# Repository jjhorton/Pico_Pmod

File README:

# Hardware
The aim of this repo is to have a PCB on which I was able to mount a standard
[Raspberry Pi Pico](https://www.raspberrypi.org/products/raspberry-pi-pico/)
and have an extended duel PMod Connector. This would allow me to connect up
the Raspberry Pi Pico upto a range of PMod Boards that I already own, as well
as to connect it upto some of the FPGA boards that I already own though there
PMod connector.

For working with the pre existing PMod Boards I've made a PMod Host board,
this hosts the accessories such as an [Seven Segment display]() or
[PMOD buttons]() 

# Software

## Host Example Software

## Client Example Software

# Licensing

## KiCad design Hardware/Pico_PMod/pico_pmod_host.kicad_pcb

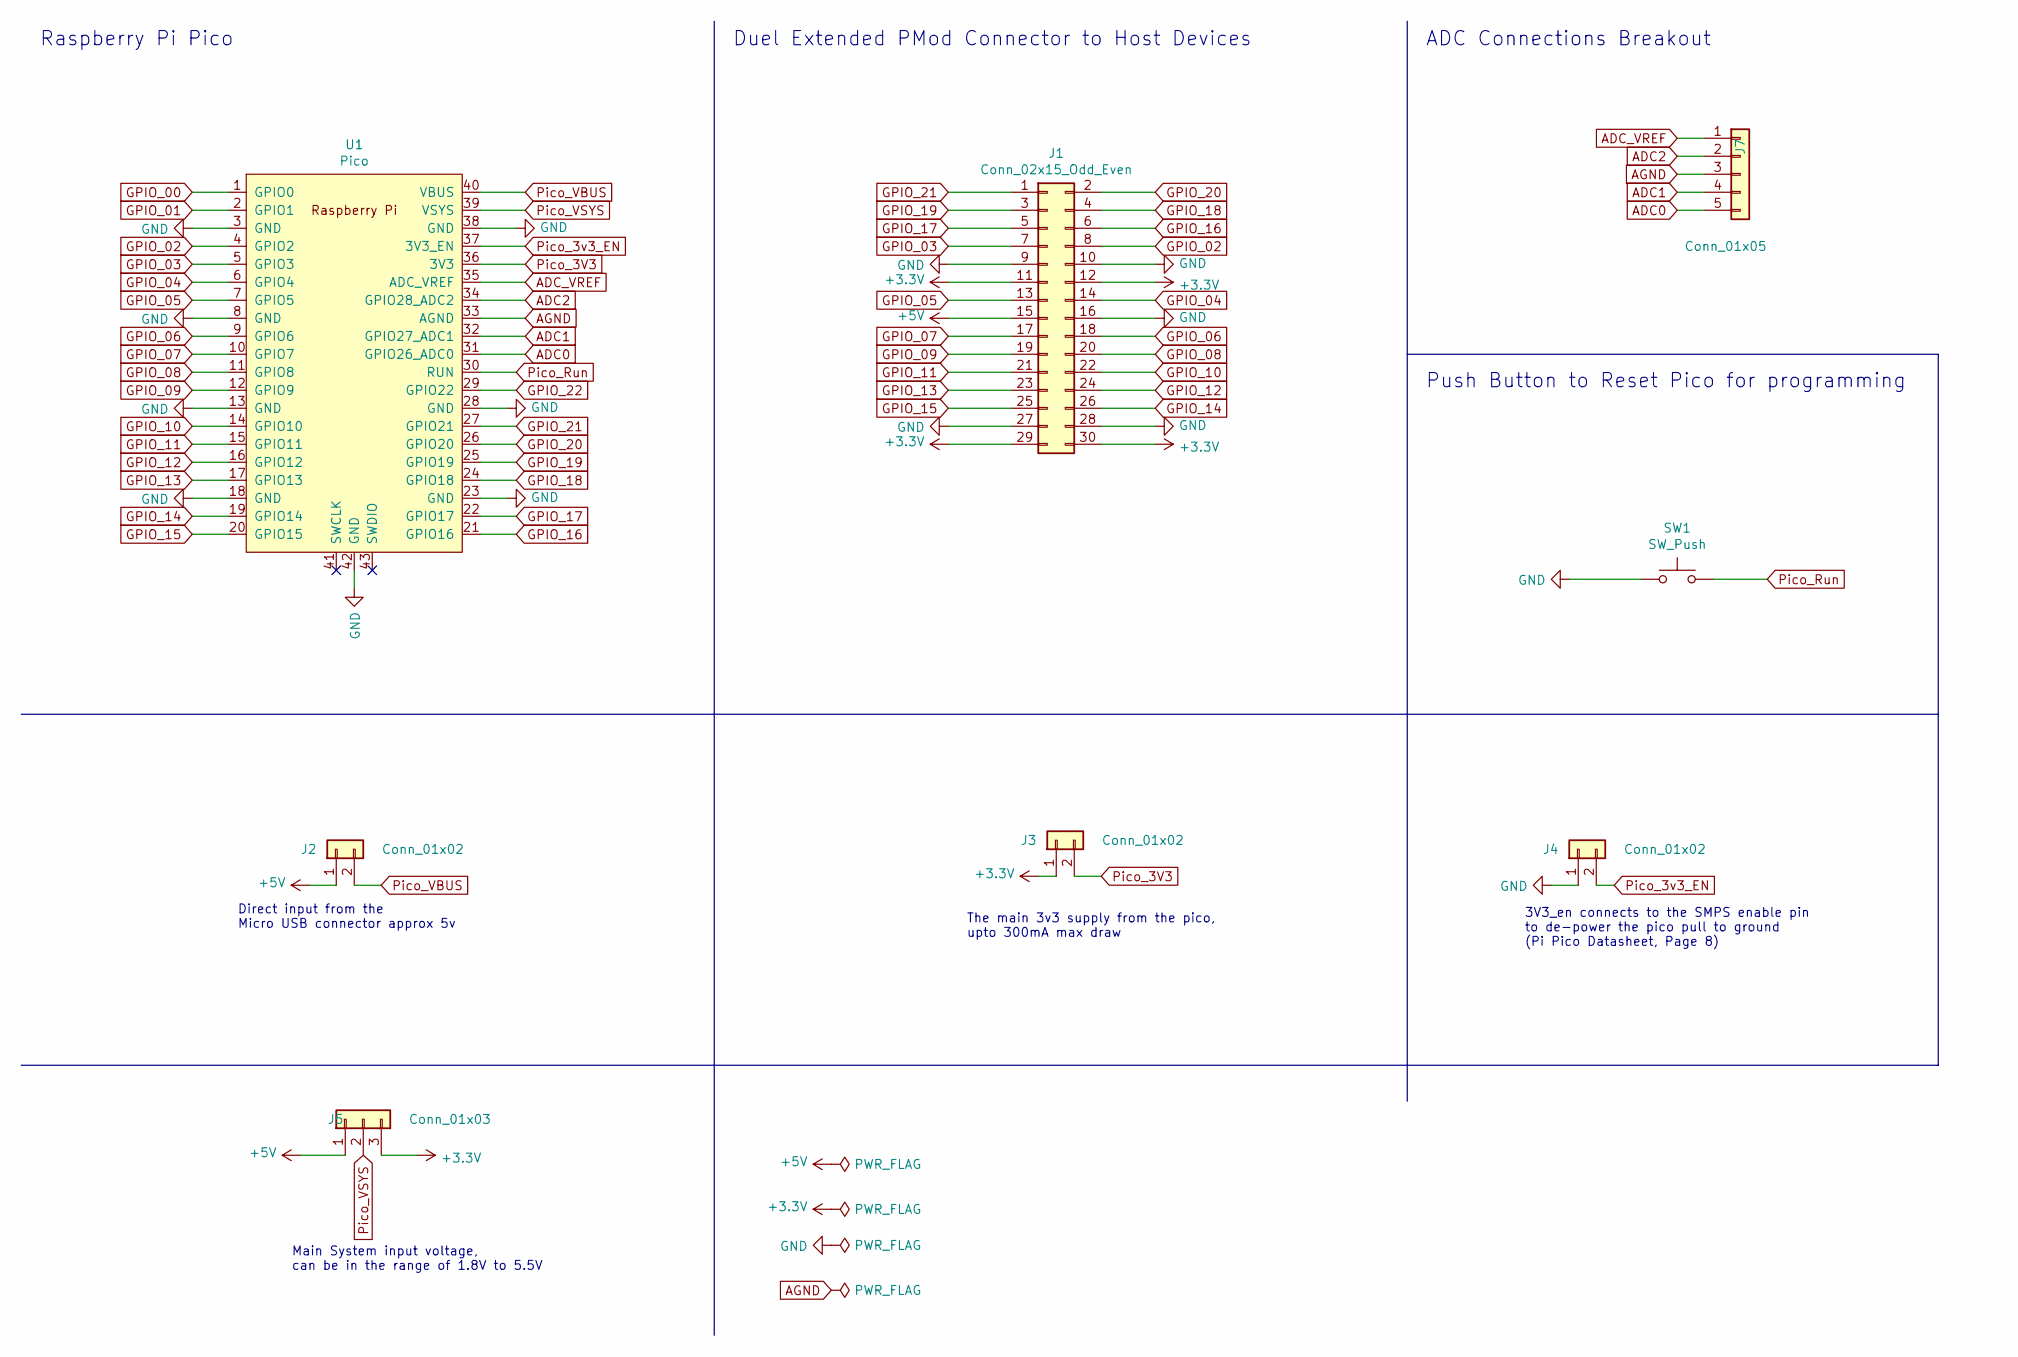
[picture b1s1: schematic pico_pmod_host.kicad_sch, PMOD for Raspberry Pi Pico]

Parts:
J1: Conn_02x15_Odd_Even; PinHeader_2x15_P2.54mm_Vertical
J2, J3, J4: Conn_01x02; PinHeader_1x02_P2.54mm_Vertical
J5: Conn_01x03; PinHeader_1x03_P2.54mm_Vertical
J7: Conn_01x05; PinHeader_1x05_P2.54mm_Vertical
SW1: SW_Push; SW_PUSH_6mm_H4.3mm
U1: Pico; RPi_Pico_SMD_TH

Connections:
+3V3: J1.11, J1.12, J1.29, J1.30, J3.1, J5.3
+5V: J1.15, J2.1, J5.1
ADC0: J7.5, U1.31 (GPIO26_ADC0)
ADC1: J7.4, U1.32 (GPIO27_ADC1)
ADC2: J7.2, U1.34 (GPIO28_ADC2)
ADC_VREF: J7.1, U1.35 (ADC_VREF)
AGND: J7.3, U1.33 (AGND)
GND: J1.9, J1.10, J1.16, J1.27, J1.28, J4.1, SW1.1, U1.3 (GND), U1.8 (GND), U1.13 (GND), U1.18 (GND), U1.23 (GND), U1.28 (GND), U1.38 (GND), U1.42 (GND)
GPIO_00: U1.1 (GPIO0)
GPIO_01: U1.2 (GPIO1)
GPIO_02: J1.8, U1.4 (GPIO2)
GPIO_03: J1.7, U1.5 (GPIO3)
GPIO_04: J1.14, U1.6 (GPIO4)
GPIO_05: J1.13, U1.7 (GPIO5)
GPIO_06: J1.18, U1.9 (GPIO6)
GPIO_07: J1.17, U1.10 (GPIO7)
GPIO_08: J1.20, U1.11 (GPIO8)
GPIO_09: J1.19, U1.12 (GPIO9)
GPIO_10: J1.22, U1.14 (GPIO10)
GPIO_11: J1.21, U1.15 (GPIO11)
GPIO_12: J1.24, U1.16 (GPIO12)
GPIO_13: J1.23, U1.17 (GPIO13)
GPIO_14: J1.26, U1.19 (GPIO14)
GPIO_15: J1.25, U1.20 (GPIO15)
GPIO_16: J1.6, U1.21 (GPIO16)
GPIO_17: J1.5, U1.22 (GPIO17)
GPIO_18: J1.4, U1.24 (GPIO18)
GPIO_19: J1.3, U1.25 (GPIO19)
GPIO_20: J1.2, U1.26 (GPIO20)
GPIO_21: J1.1, U1.27 (GPIO21)
GPIO_22: U1.29 (GPIO22)
Pico_3V3: J3.2, U1.36 (3V3)
Pico_3v3_EN: J4.2, U1.37 (3V3_EN)
Pico_Run: SW1.2, U1.30 (RUN)
Pico_VBUS: J2.2, U1.40 (VBUS)
Pico_VSYS: J5.2, U1.39 (VSYS)

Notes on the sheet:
Duel Extended PMod Connector to Host Devices
Main System input voltage, can be in the range of 1.8V to 5.5V
3V3_en connects to the SMPS enable pin to de-power the pico pull to ground (Pi Pico Datasheet, Page 8)
The main 3v3 supply from the pico, upto 300mA max draw
Push Button to Reset Pico for programming
ADC Connections Breakout
Direct input from the Micro USB connector approx 5v
Raspberry Pi Pico

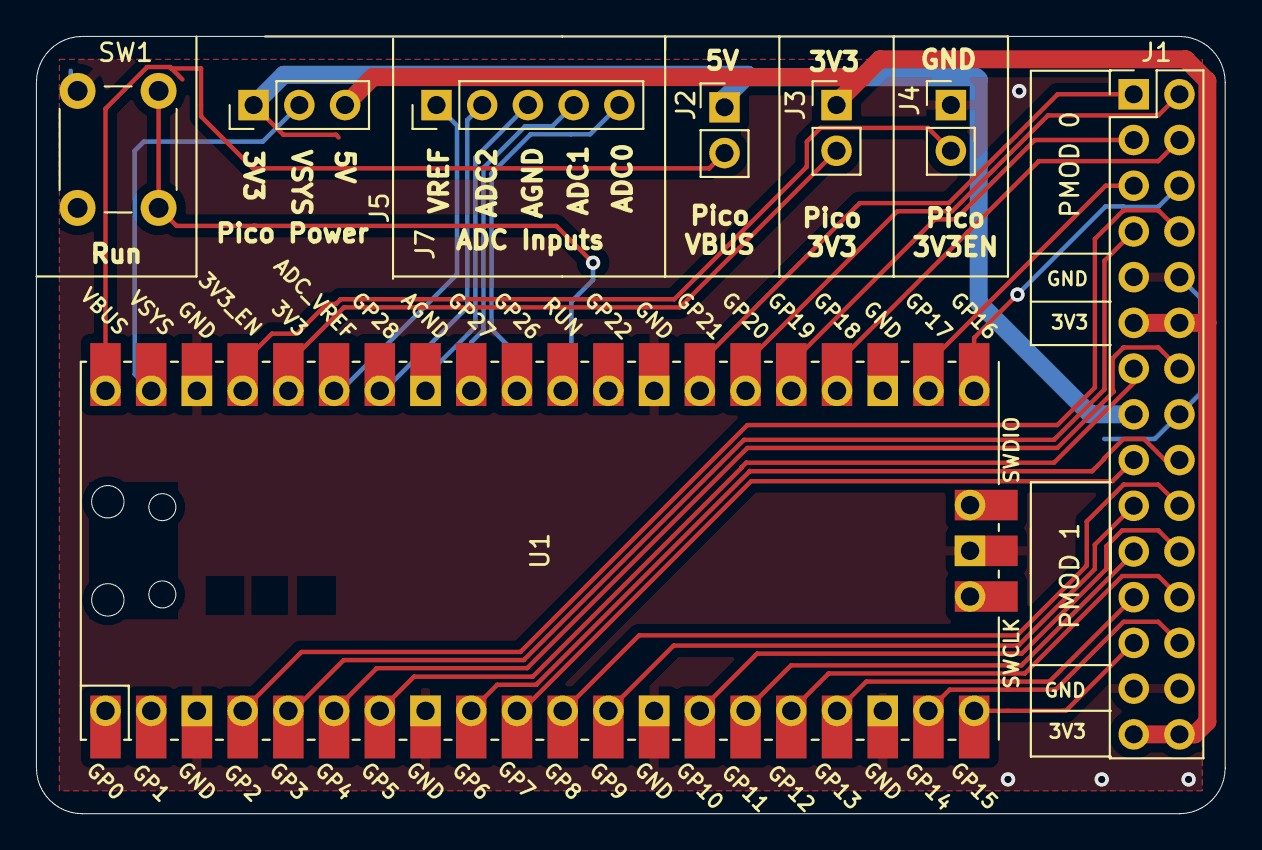
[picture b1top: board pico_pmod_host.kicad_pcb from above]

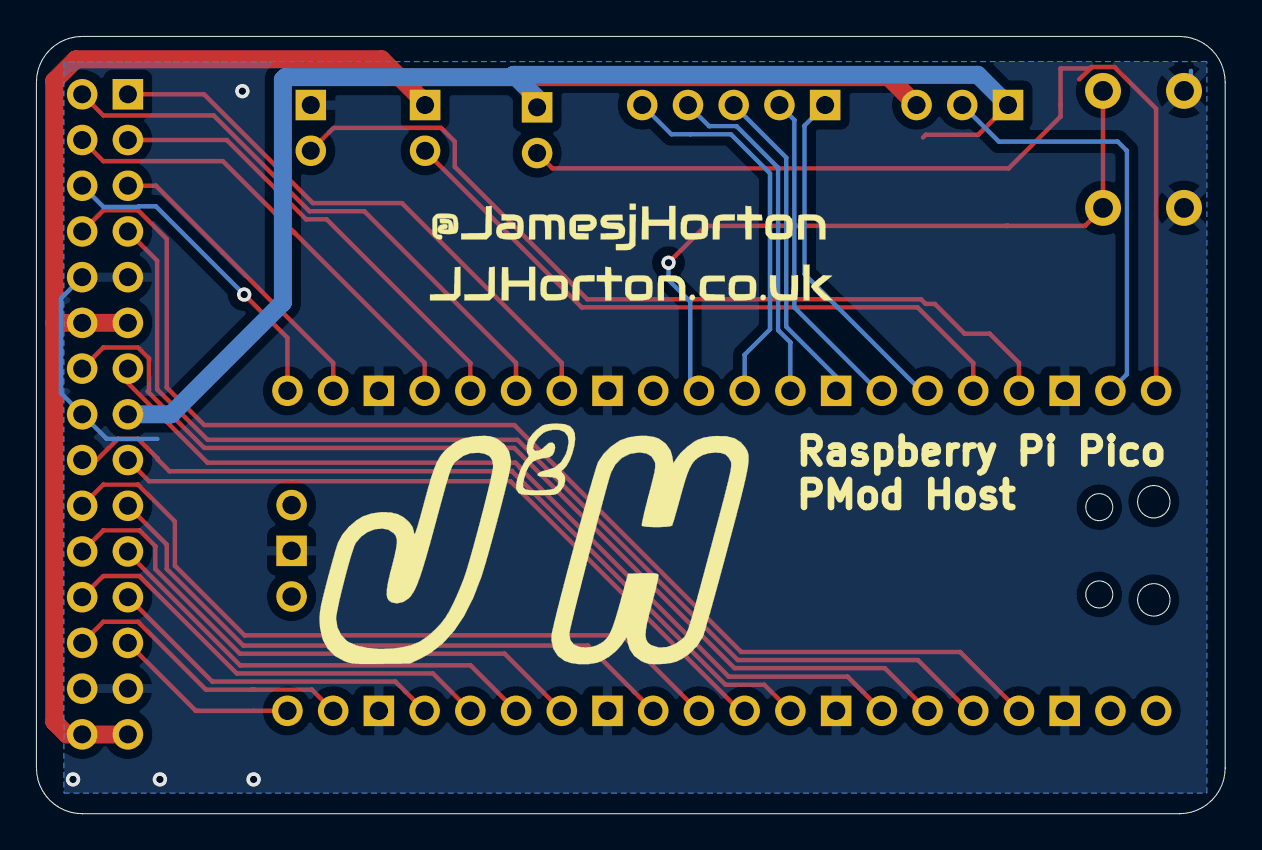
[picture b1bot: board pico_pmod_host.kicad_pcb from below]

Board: 2 copper layers, 66.0 x 43.2 mm, 10 parts (2 on the bottom side), 33 nets.

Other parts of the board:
Logo1: LOGO; Untitled
Logo2: LOGO; ContactDetails_small

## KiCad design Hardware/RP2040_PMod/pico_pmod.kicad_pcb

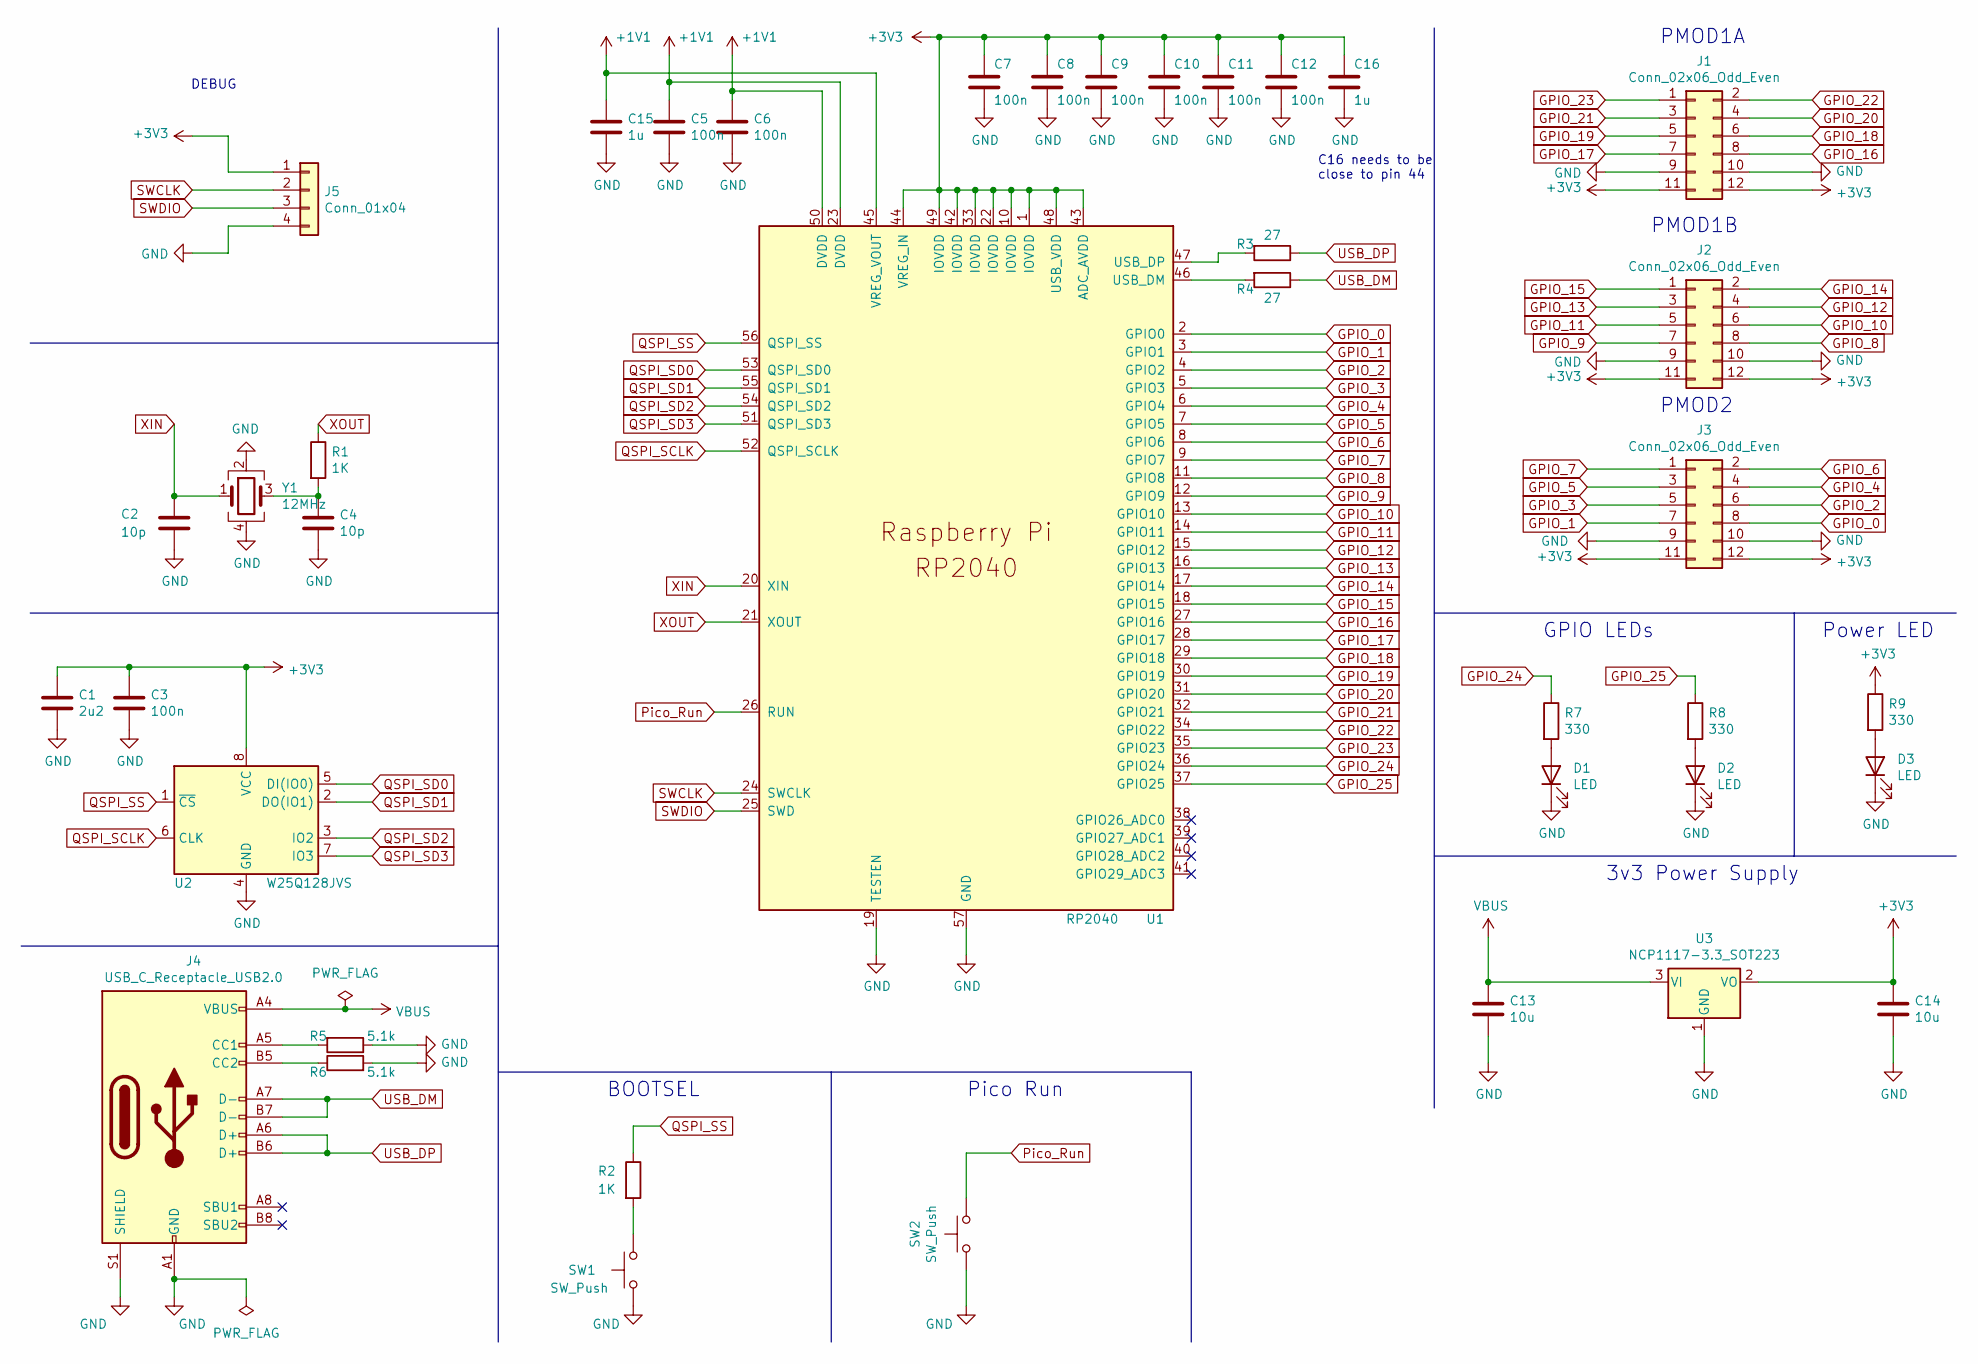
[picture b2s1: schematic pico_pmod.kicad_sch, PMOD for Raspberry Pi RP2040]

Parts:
C1: 2u2; C_0603_1608Metric
C2, C4: 10p; C_0603_1608Metric
C3, C5, C6, C7, C8, C9, C10, C11, C12: 100n; C_0603_1608Metric
C13, C14: 10u; C_0603_1608Metric
C15, C16: 1u; C_0603_1608Metric
D1, D2, D3: LED; LED_0603_1608Metric
J1, J2, J3: Conn_02x06_Odd_Even; PinHeader_2x06_P2.54mm_Vertical
J4: USB_C_Receptacle_USB2.0; USB_C_Receptacle_Amphenol_12401610E4-2A_CircularHoles
J5: Conn_01x04; PinHeader_1x04_P2.54mm_Vertical
R1, R2: 1K; R_0603_1608Metric
R3, R4: 27; R_0603_1608Metric
R5, R6: 5.1k; R_0603_1608Metric
R7, R8, R9: 330; R_0603_1608Metric
SW1, SW2: SW_Push; SW_PUSH_6mm_H4.3mm
U1: RP2040; RP2040-QFN-56
U2: W25Q128JVS; SOIC-8_5.23x5.23mm_P1.27mm
U3: NCP1117-3.3_SOT223; SOT-223-3_TabPin2
Y1: 12MHz; Crystal_SMD_SeikoEpson_FA238-4Pin_3.2x2.5mm

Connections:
+1V1: C5.1, C6.1, C15.1, U1.23 (DVDD), U1.45 (VREG_VOUT), U1.50 (DVDD)
+3V3: C1.1, C3.1, C7.1, C8.1, C9.1, C10.1, C11.1, C12.1, C14.1, C16.1, J1.11, J1.12, J2.11, J2.12, J3.11, J3.12, J5.1, R9.1, U1.1 (IOVDD), U1.10 (IOVDD), U1.22 (IOVDD), U1.33 (IOVDD), U1.42 (IOVDD), U1.43 (ADC_AVDD), U1.44 (VREG_IN), U1.48 (USB_VDD), U1.49 (IOVDD), U2.8 (VCC), U3.2 (VO)
GND: C1.2, C2.2, C3.2, C4.2, C5.2, C6.2, C7.2, C8.2, C9.2, C10.2, C11.2, C12.2, C13.2, C14.2, C15.2, C16.2, D1.1 (K), D2.1 (K), D3.1 (K), J1.9, J1.10, J2.9, J2.10, J3.9, J3.10, J4.A1 (GND), J4.A12 (GND), J4.B1 (GND), J4.B12 (GND), J4.S1 (SHIELD), J5.4, R5.1, R6.2, SW1.1, SW2.1, U1.19 (TESTEN), U1.57 (GND), U2.4 (GND), U3.1 (GND), Y1.2, Y1.4
GPIO_0: J3.8, U1.2 (GPIO0)
GPIO_1: J3.7, U1.3 (GPIO1)
GPIO_2: J3.6, U1.4 (GPIO2)
GPIO_3: J3.5, U1.5 (GPIO3)
GPIO_4: J3.4, U1.6 (GPIO4)
GPIO_5: J3.3, U1.7 (GPIO5)
GPIO_6: J3.2, U1.8 (GPIO6)
GPIO_7: J3.1, U1.9 (GPIO7)
GPIO_8: J2.8, U1.11 (GPIO8)
GPIO_9: J2.7, U1.12 (GPIO9)
GPIO_10: J2.6, U1.13 (GPIO10)
GPIO_11: J2.5, U1.14 (GPIO11)
GPIO_12: J2.4, U1.15 (GPIO12)
GPIO_13: J2.3, U1.16 (GPIO13)
GPIO_14: J2.2, U1.17 (GPIO14)
GPIO_15: J2.1, U1.18 (GPIO15)
GPIO_16: J1.8, U1.27 (GPIO16)
GPIO_17: J1.7, U1.28 (GPIO17)
GPIO_18: J1.6, U1.29 (GPIO18)
GPIO_19: J1.5, U1.30 (GPIO19)
GPIO_20: J1.4, U1.31 (GPIO20)
GPIO_21: J1.3, U1.32 (GPIO21)
GPIO_22: J1.2, U1.34 (GPIO22)
GPIO_23: J1.1, U1.35 (GPIO23)
GPIO_24: R7.1, U1.36 (GPIO24)
GPIO_25: R8.1, U1.37 (GPIO25)
unnamed: C4.1, R1.2, Y1.3
unnamed: D1.2 (A), R7.2
unnamed: D2.2 (A), R8.2
unnamed: D3.2 (A), R9.2
unnamed: J4.A5 (CC1), R5.2
unnamed: J4.B5 (CC2), R6.1
unnamed: R2.2, SW1.2
unnamed: R3.2, U1.47 (USB_DP)
unnamed: R4.2, U1.46 (USB_DM)
Pico_Run: SW2.2, U1.26 (RUN)
QSPI_SCLK: U1.52 (QSPI_SCLK), U2.6 (CLK)
QSPI_SD0: U1.53 (QSPI_SD0), U2.5 (DI(IO0))
QSPI_SD1: U1.55 (QSPI_SD1), U2.2 (DO(IO1))
QSPI_SD2: U1.54 (QSPI_SD2), U2.3 (IO2)
QSPI_SD3: U1.51 (QSPI_SD3), U2.7 (IO3)
QSPI_SS: R2.1, U1.56 (QSPI_SS), U2.1 (~CS)
SWCLK: J5.2, U1.24 (SWCLK)
SWDIO: J5.3, U1.25 (SWD)
USB_DM: J4.A7 (D-), J4.B7 (D-), R4.1
USB_DP: J4.A6 (D+), J4.B6 (D+), R3.1
VBUS: C13.1, J4.A4 (VBUS), J4.A9 (VBUS), J4.B4 (VBUS), J4.B9 (VBUS), U3.3 (VI)
XIN: C2.1, U1.20 (XIN), Y1.1
XOUT: R1.1, U1.21 (XOUT)

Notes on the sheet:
Pico Run
PMOD1B
Power LED
DEBUG
GPIO LEDs
3v3 Power Supply
PMOD2
PMOD1A
BOOTSEL
C16 needs to be close to pin 44

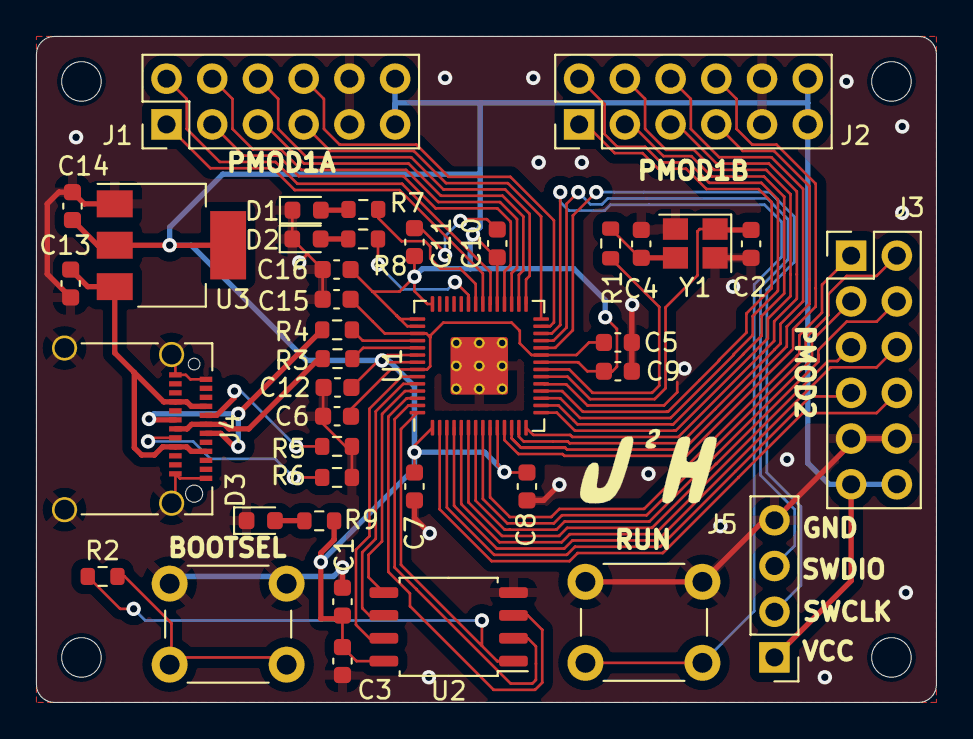
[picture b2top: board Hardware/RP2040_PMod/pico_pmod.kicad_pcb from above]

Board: 2 copper layers, 50.0 x 37.0 mm, 45 parts (1 on the bottom side), 52 nets.

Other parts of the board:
Hole1, Hole2, Hole3, Hole4: MountingHole_2.2mm_M2
L1: LOGO; j2h_small
L2: LOGO; Untitled

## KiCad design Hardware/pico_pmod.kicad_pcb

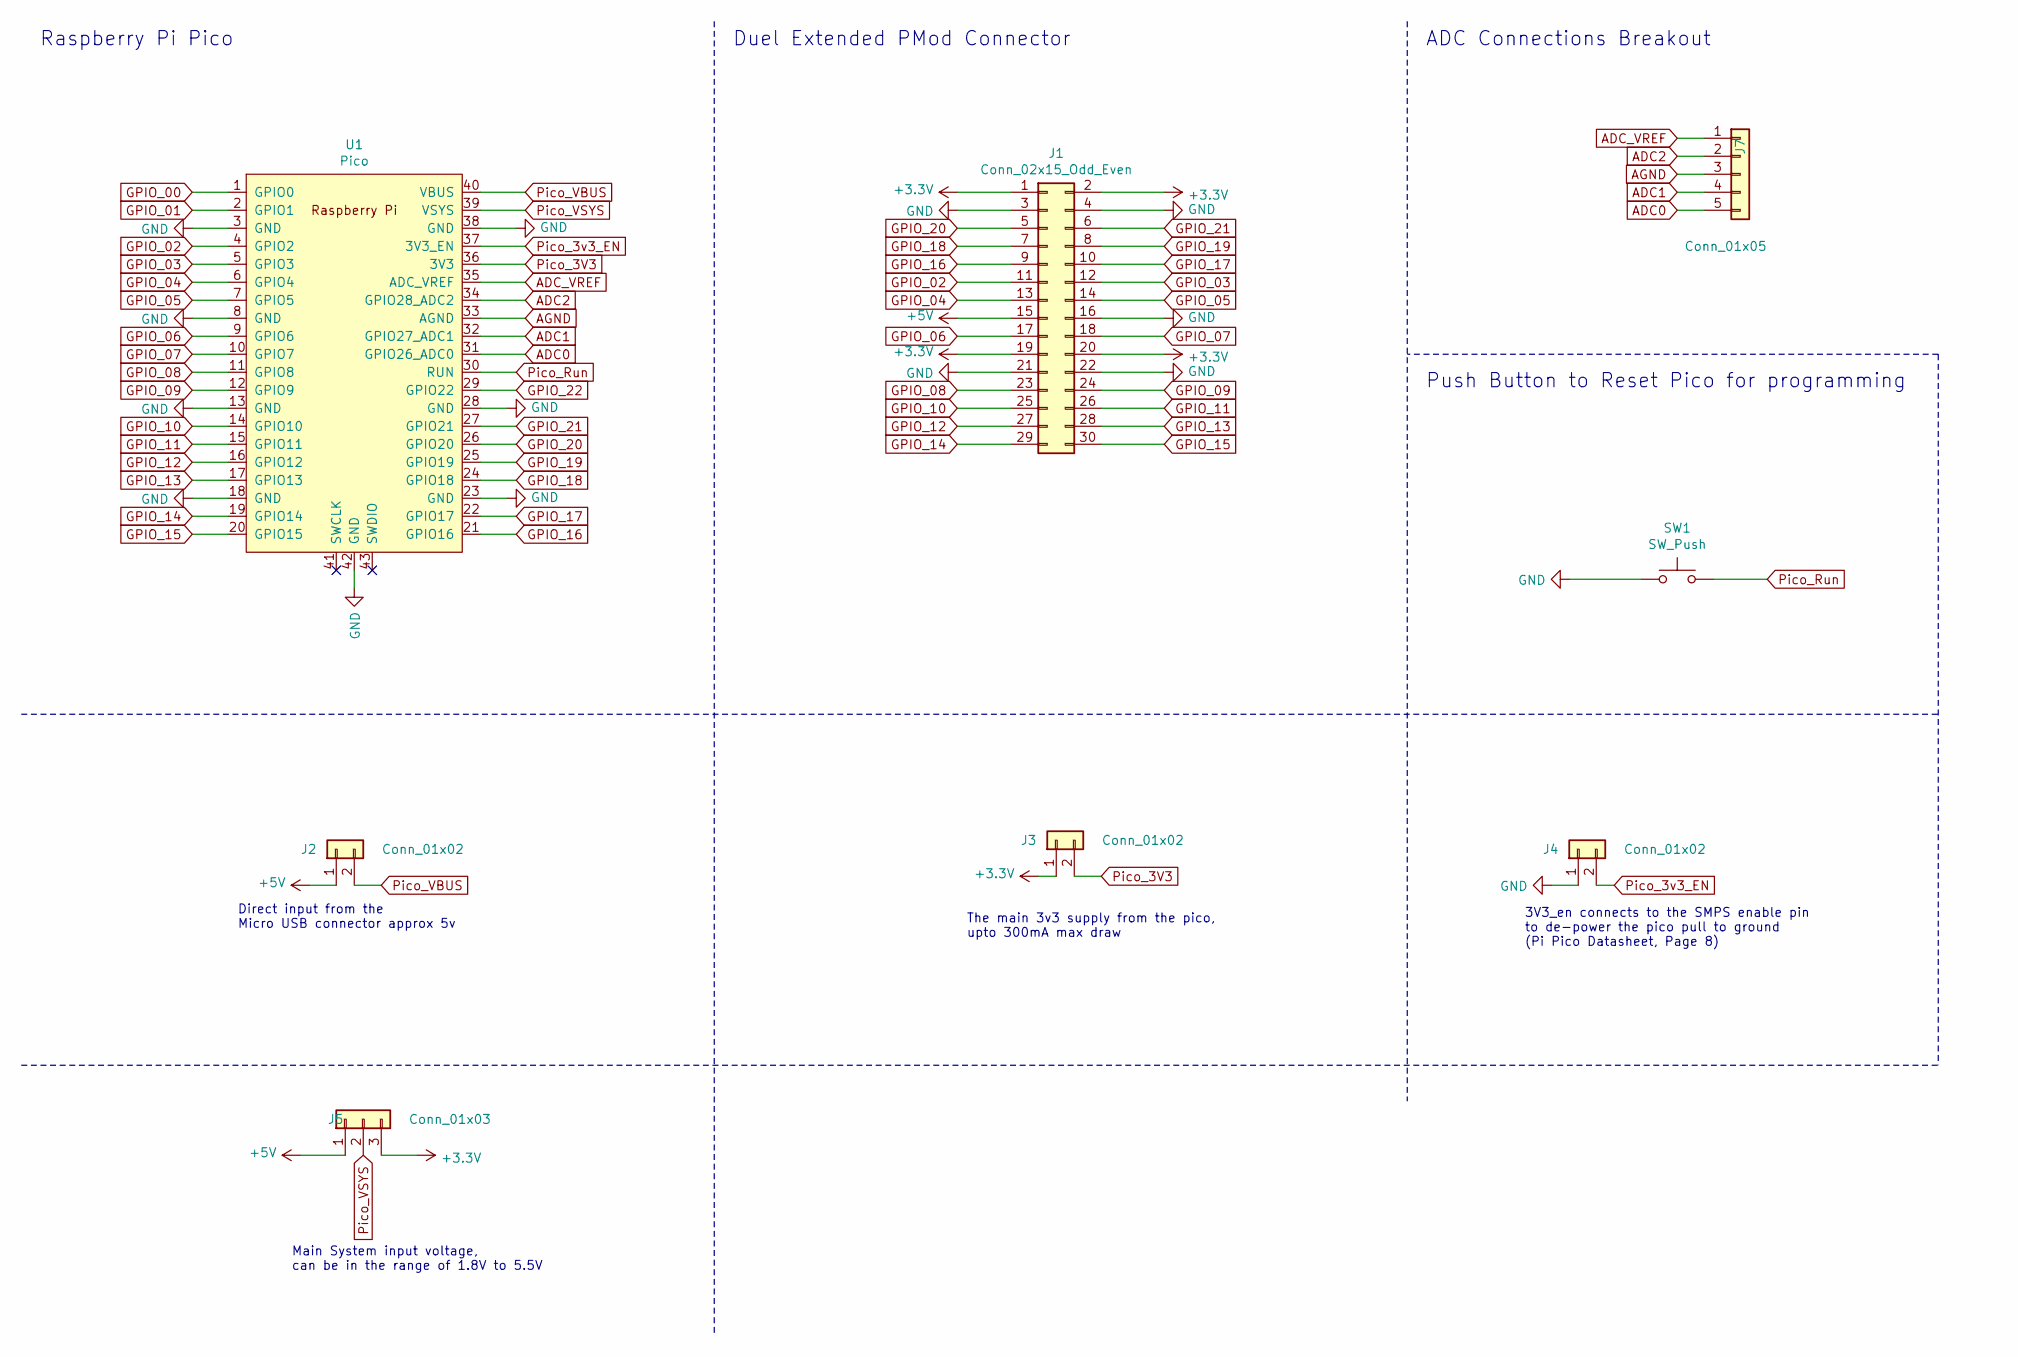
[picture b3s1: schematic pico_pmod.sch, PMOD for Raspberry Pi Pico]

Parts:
J1: Conn_02x15_Odd_Even; PinHeader_2x15_P2.54mm_Vertical
J2, J3, J4: Conn_01x02; PinHeader_1x02_P2.54mm_Vertical
J5: Conn_01x03; PinHeader_1x03_P2.54mm_Vertical
J7: Conn_01x05; PinHeader_1x05_P2.54mm_Vertical
SW1: SW_Push; SW_PUSH_6mm_H4.3mm
U1: Pico; RPi_Pico_SMD_TH

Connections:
+3V3: J1.1, J1.2, J1.19, J1.20, J3.1, J5.3
+5V: J1.15, J2.1, J5.1
ADC0: J7.5, U1.31 (GPIO26_ADC0)
ADC1: J7.4, U1.32 (GPIO27_ADC1)
ADC2: J7.2, U1.34 (GPIO28_ADC2)
ADC_VREF: J7.1, U1.35 (ADC_VREF)
AGND: J7.3, U1.33 (AGND)
GND: J1.3, J1.4, J1.16, J1.21, J1.22, J4.1, SW1.1, U1.3 (GND), U1.8 (GND), U1.13 (GND), U1.18 (GND), U1.23 (GND), U1.28 (GND), U1.38 (GND), U1.42 (GND)
GPIO_00: U1.1 (GPIO0)
GPIO_01: U1.2 (GPIO1)
GPIO_02: J1.11, U1.4 (GPIO2)
GPIO_03: J1.12, U1.5 (GPIO3)
GPIO_04: J1.13, U1.6 (GPIO4)
GPIO_05: J1.14, U1.7 (GPIO5)
GPIO_06: J1.17, U1.9 (GPIO6)
GPIO_07: J1.18, U1.10 (GPIO7)
GPIO_08: J1.23, U1.11 (GPIO8)
GPIO_09: J1.24, U1.12 (GPIO9)
GPIO_10: J1.25, U1.14 (GPIO10)
GPIO_11: J1.26, U1.15 (GPIO11)
GPIO_12: J1.27, U1.16 (GPIO12)
GPIO_13: J1.28, U1.17 (GPIO13)
GPIO_14: J1.29, U1.19 (GPIO14)
GPIO_15: J1.30, U1.20 (GPIO15)
GPIO_16: J1.9, U1.21 (GPIO16)
GPIO_17: J1.10, U1.22 (GPIO17)
GPIO_18: J1.7, U1.24 (GPIO18)
GPIO_19: J1.8, U1.25 (GPIO19)
GPIO_20: J1.5, U1.26 (GPIO20)
GPIO_21: J1.6, U1.27 (GPIO21)
GPIO_22: U1.29 (GPIO22)
Pico_3V3: J3.2, U1.36 (3V3)
Pico_3v3_EN: J4.2, U1.37 (3V3_EN)
Pico_Run: SW1.2, U1.30 (RUN)
Pico_VBUS: J2.2, U1.40 (VBUS)
Pico_VSYS: J5.2, U1.39 (VSYS)

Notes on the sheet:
Direct input from the Micro USB connector approx 5v
Main System input voltage, can be in the range of 1.8V to 5.5V
3V3_en connects to the SMPS enable pin to de-power the pico pull to ground (Pi Pico Datasheet, Page 8)
The main 3v3 supply from the pico, upto 300mA max draw
Raspberry Pi Pico
Duel Extended PMod Connector
ADC Connections Breakout
Push Button to Reset Pico for programming

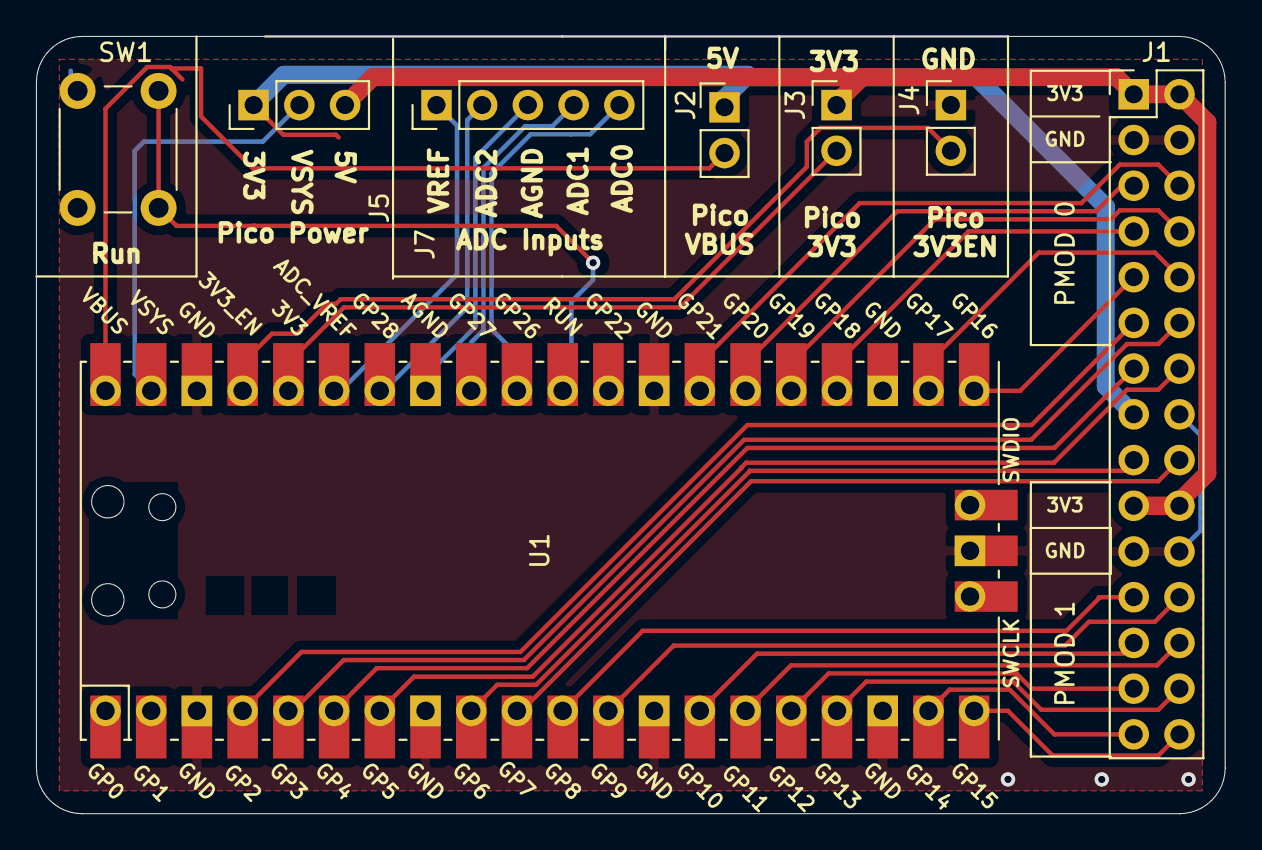
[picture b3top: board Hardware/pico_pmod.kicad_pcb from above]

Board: 2 copper layers, 66.0 x 43.2 mm, 8 parts (0 on the bottom side), 33 nets.

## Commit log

2021-04-15 inital commit of schematic and board
2021-04-15 add power pin headers and initial layout work
2021-04-15 finish layout, start of silk screen
2021-04-16 sort out keepout areas for ground plane on board top
2021-04-16 breakout ADC inputs to pins
2021-04-16 minor silkscreen changes before ordering
2021-04-20 Add some initial pico build example that flashes an LED
2021-04-20 Minor circuit changes
2021-04-21 Change to setup pins from an array instead of directly
2021-04-21 Change code to be downward binary counter in uint8_t datatype
2021-04-21 Add the git ignore file
2021-04-21 Add PDF version of the Schematic to the repo
2021-04-22 Add Reset button to the Pico Schematic
2021-04-22 Add Run switch to the PCB
2021-04-22 Remove Run Header pins
2021-04-22 move existing design to client folder
2021-04-22 create files for the host version
2021-04-22 rotate the connector to match the pmod pins when hosting
2021-04-22 PMOD connector corrected to match schematic
2021-04-29 Minor changes to both PCB layouts
2021-04-29 Add the 7 segment counter
2021-04-30 Move the progam into its own Counter folder
2021-04-30 Change the location of the buils files
2021-04-30 Add initial version of the build buttons code
2021-04-30 Update the copyright notice
2021-04-30 Update the copyright notice from the initial example
2021-04-30 Add zip files to stop them being added to repo
2021-05-03 reorder the buttons into the correct order
2021-05-03 correct the button pin mappings
2021-05-03 update the 5v pinout on the pmod connector for #1 on the host board
2021-05-03 update the 5v pinout on the pmod connector for #1 on the PCB
2021-05-03 Add an outline to the repo README file
2021-05-03 Format readme as a markdown file
2021-05-03 Add introduction and some additional details to hardware description
2021-05-04 Change the logo on the host board
2021-05-10 Create a seperate function for set display
2021-05-10 Remove the unused element of the main function
2021-05-10 Correct an error in the hash define
2021-05-10 move the display functionality out into there own functions
2021-05-10 Add the defined if statement for the different pmod connectors
2021-05-10 reduce the wait counter, and remove white space
2021-06-08 Add CI outline for the Host Pmod Board
2021-06-08 Kibot config file inital version
2021-06-08 Add JLC output to the file
2021-06-08 rename kibot config file so they match
2021-06-08 correct the sch and pcb file names
2021-06-08 Remove the spreadsheet XLSC bom which isnt needed
2021-06-08 remove unused image
2021-06-08 Add production file generation for the client files
2021-07-09 initial schematic work for custom Pmod Board
2021-07-09 add capasitor details
2021-07-12 initial functional PCB layout
2021-07-12 Add the switchs footprints and put on PCB
2021-07-12 Add usb CC 1 and 2 resistors
2021-07-13 Add power supply and spi memory
2021-07-13 Add the USB resitors and route power supply
2021-07-13 Add the debug port footprint
2021-07-14 PCB layout for PMOD1B and PMOD2
2021-07-14 Make headers virtual parts so they are not in 3D step models
2021-07-16 Add connections to PMOD1A connector
2021-07-16 update with ground plane and LED's
2021-07-16 Add the logo and text onto back of the PCB
2021-07-16 Add lables to the Debug Port
2021-07-16 Add workflow file for the Custom RP2040 Board
2021-07-16 mark unused pins as not connected
2021-07-16 fix DRC errors with 3v3 power
2021-07-16 Add filter for DRC of the USB pads
2021-07-16 Ensure that pins 48 and 49 are connected to 3v3
2021-07-16 Update the name of github workflow
2021-07-16 update kibot to generated step models and PCB Draw Files
2021-07-16 Remove Global spelling error
2021-07-16 update resistor values from schimatic
2021-08-05 Correct USB DP and DN for #7
2021-08-05 Correct USB DP and DN on PCB for #7
2021-08-06 Add logo on front of board and straight PMod tracks
2021-08-11 edit the PMOD traces to straighten them
2021-08-12 Update the readme with details of the RP2040 PMod Board
2021-08-12 Add the Build status for the CI onto the Readme page
2021-08-17 Rename the Custom PMod Board
2021-08-17 remove Client and rename Host to Pico PMod
2021-08-17 Remove unused client build flow
2021-08-17 Update the paths to reflect the folder name changes
2021-08-17 update the paths for the Pico PMod Hardware
2021-08-28 minor hardware improvments
2021-08-28 Fix the Pmod RP2040 board workflow
2021-08-28 Update the status badges for the workflows
2021-09-06 add back of a case to hold RP2040 PMod board
2021-09-20 Generating a backing case for the RP2040 Board
2021-11-24 Update the clk Caps
2021-11-29 Add a hardware Licence file
    Add license file for the hardware
2021-11-29 Add a software license
2021-11-29 Add software license description to the main.c files for the examples
2021-11-29 Rename hardware license
2021-11-30 Update with the license statement
2021-11-30 Add descipriotn to the PCB Boards
2021-11-30 Update the title for the RP2040 PCB Board
2021-11-30 Add descriptions and titles to the PCB sheets
2021-12-06 Update readme software text
2021-12-06 Add details of the RP2040 board to the repo
2021-12-06 Add mouser links into software description
2022-01-13 Update Pico PMod workflow to run once a week on a monday at 8am
2022-01-13 remove run on push request
2022-01-13 Update RP2040 PMod workflow to run once a week on a monday at 8am
2022-01-25 update github workflow for kicad6
2022-01-25 remove creation fo hardware folder
2022-01-25 correct kicad schematic file name
2022-01-25 add power flags to schematic for ERC
2022-01-25 reroute usb-c (j4) gnd to avoid DRC issue
2022-01-25 Correct DRC warning for unconnected tracks and overlapping silkscreen
2022-01-25 Swap pin header 3d model for pin socket models
2022-01-26 Update the paths to 3d models to use a referencet to own library
2022-02-02 update 3D parts to use my custom models
2022-02-02 correct scaling for the rp2040
2022-06-15 Add the pico pmod board image
2022-06-15 Add rp2040 board image
2022-06-15 update the readme with the pictures
2022-06-15 move pictures into a table
2022-06-27 add streamlined workflow for v6 kicad
2022-06-27 correct the location of the workflow file
2022-06-27 use kibot v2_d for kicad v5 project
2022-06-27 correct the file name for workflow run
2022-10-16 update workflow to use github action
2022-10-16 Change to use kicad v6
2022-10-16 Update the filename
2022-10-16 version bump to v2 kibot
2022-10-16 v5 should not be specified
2022-10-16 Set additional_args to empty
2022-10-16 Test with dev version
2022-10-16 go back to stable version
2022-10-18 correct the kibot config file location
2022-10-18 correct the filename for yml file
2023-01-03 add initial attempt at mini board
2023-01-03 continue with mini project
2023-01-03 Add the SD GPIO and RGB LED to schematic
2023-01-04 complete schematic and start pcb routing
2023-01-04 update switch layout and sd card gnd pins
2023-01-05 remove usb sheild from usb connector
2023-01-05 update button footprint and fix some drc errors
2023-01-05 add workflow file for CI
2023-01-05 update the 3d models for switches
2023-01-05 replace 3d model for RP2040 and add 3d model for rgb LEDs
2023-01-06 PCB art work
2023-01-06 add githash to back of PCB
2023-01-06 add the githash update code to the workflow file
2023-01-06 correct filename of file to replace githash value
2023-01-06 first attempt at the panel
2023-01-06 correct to needs
2023-01-06 need to checkout the repo and update the files
2023-01-06 update so the panel files includes a schematic
2023-01-06 set to skip erc and drc on panel
2023-01-06 remove skip erc for panel
2023-01-06 add all to preflight and remove kibot apt get
2023-01-06 update to install kicad v6.0 from kicad release
2023-01-06 add targets to the output list
2023-01-06 remove brackets
2023-01-06 just generate the jlc gerbers
2023-01-06 add interactive_bon and board_top
2023-01-06 remove the horizontal grid
2023-01-06 change to 3 rows and 2 cols
2023-01-06 move mousebite holes onto tabss
2023-01-06 extend the tabs between panelled boards
2023-01-06 update to add text to panels for processing
2023-01-06 edit the text format
2023-01-06 increase tab width to 5mm
2023-01-06 remove colon from pcb text
2023-01-10 increase the space around the usb-c corrector
2023-01-10 fix uneven sides of the usb connector
2023-01-11 edit board outline
2023-01-16 update with new 3d model for rp2040
2023-01-17 minor PCB changes to 3D model
2023-01-17 Add FreeCad Model generated from kicad board
2023-02-06 correct 3v3 issue for #31 with LED's
2023-02-06 include the correction on the pcb layout
2023-02-26 add image of all 3 boards
2023-02-26 update description table with mini Pmod
2023-02-26 Add the picture of the three boards to the readme file
2024-02-17 upgrade to kicad 7.0
2024-02-17 Upgrade workflow to v7
2024-02-17 enable ignore unconnected pads
2024-02-17 html bom changes
2024-02-17 Change reference for error
2024-02-17 change reference for logo
2024-02-17 change spacing
2024-02-17 change REF to Mount
2024-02-18 Update schematic to kicad7
2024-02-18 Update PCB to kicad7
2024-02-18 update workflow to kicad 7
2024-02-18 remove the Ref on the holes
2024-02-18 change logo designator
2024-02-18 update workflow to kicad7
2024-02-18 update connector j1
2024-02-18 remove old lib file
2024-02-18 update workflow file
2024-02-18 update the logo reference
2024-02-18 remove old files for kicad v5
2024-05-14 add kicanvas links for the boards
2024-05-14 add manual run to workflows
2024-05-14 correct spelling
2024-09-23 udate to v4 upload
2024-09-23 change panel fab files name
2024-09-24 rename the fab files for panel
2024-10-16 Add JLC Part numbers
2024-10-16 Add JLC Bom generation
2024-10-16 change to use LCSC part number
2024-10-16 Add JLC Bom filter
2024-10-16 update to include more components

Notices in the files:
Hardware/Pico_PMod/pico_pmod_host.kicad_pcb:
Licensed Under CERN Open Hardware Licence Version 2 - Permissive
